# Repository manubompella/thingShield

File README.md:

# Arduino XBee shield

The Arduino shield is designed to be used for multiple use cases without redesigning the hardware. 

## Platform Features

 * [XBee Compatible Socket](https://www.sparkfun.com/datasheets/Wireless/Zigbee/XBee-Dimensional.pdf)
 * TTL to CMOS level shifter
 * Compatible with UNO R3 headers
 * Ability to support multiple thingBot platforms
 
## Maintainers

The Arduino Xbee shield is maintained by thingTronics Innovations.

Main contributor:
 * Manohar Bompella @<manohar.bompella@thingtronics.com>
 * Lovelesh Patel @<lovelesh.patel@thingtronics.com>

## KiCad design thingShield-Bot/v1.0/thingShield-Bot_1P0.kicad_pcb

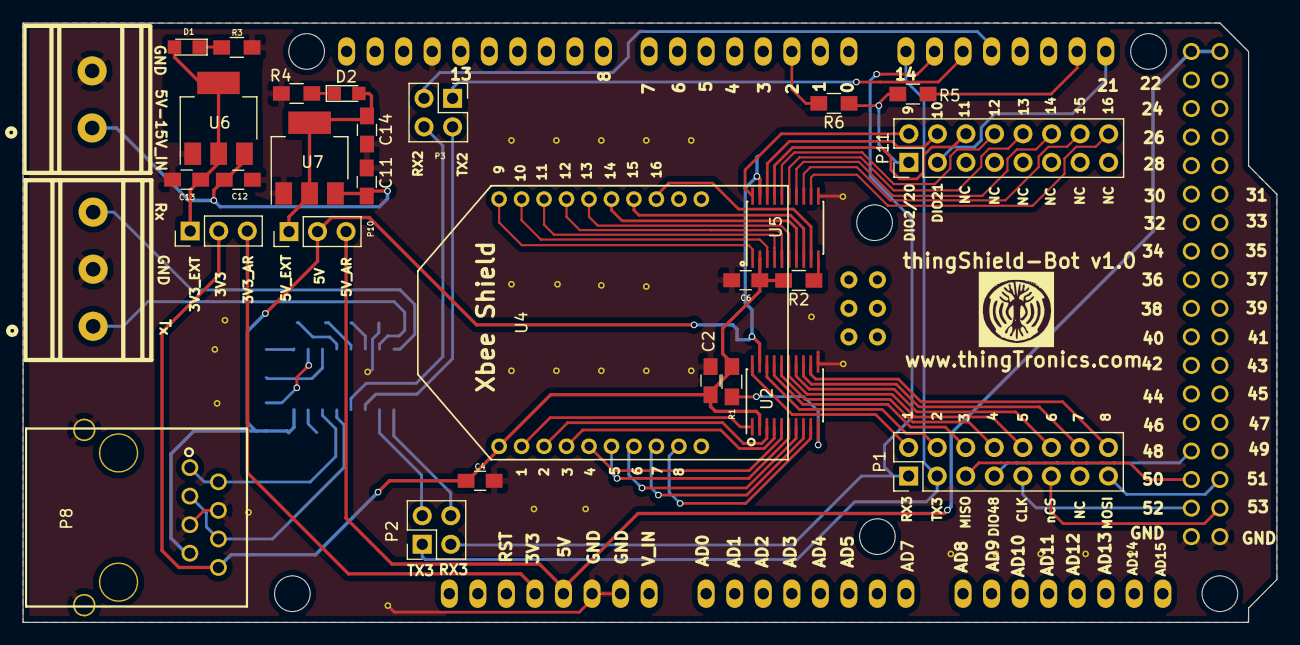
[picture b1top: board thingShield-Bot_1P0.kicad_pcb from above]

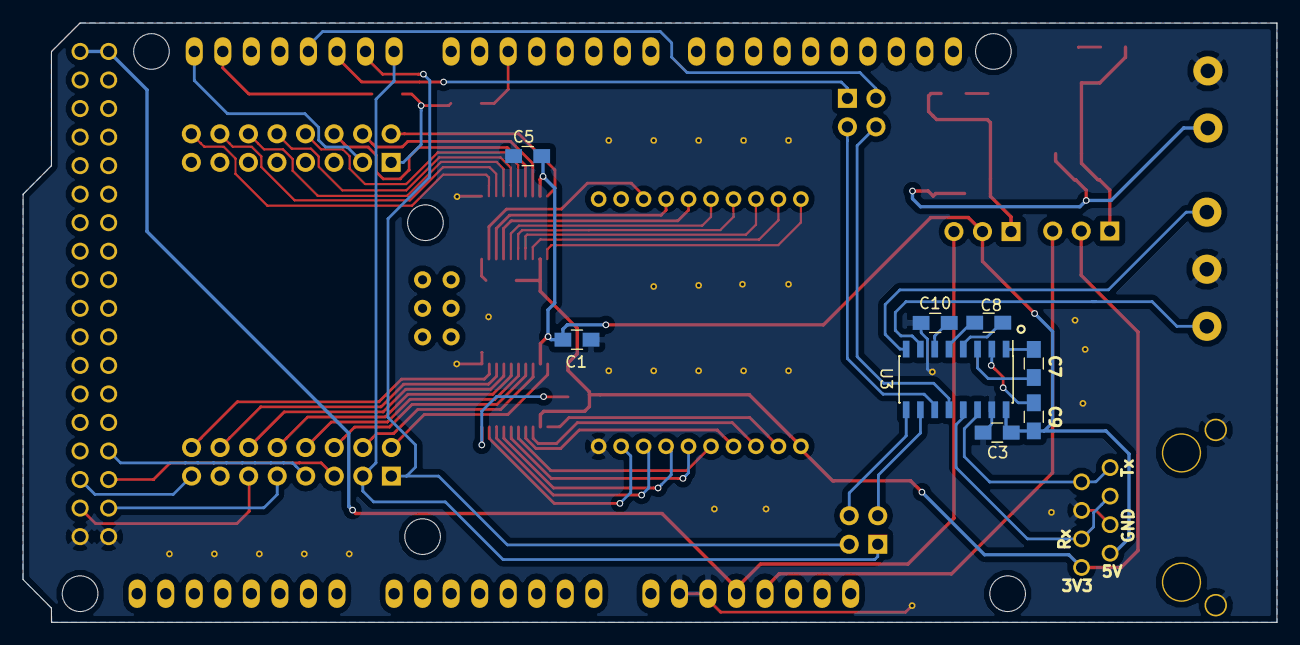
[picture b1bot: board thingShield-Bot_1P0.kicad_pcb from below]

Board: 2 copper layers, 111.6 x 53.3 mm, 38 parts (8 on the bottom side), 71 nets.

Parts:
C1, C2, C5, C6: 0.1uF; C_0805_HandSoldering
C3, C4, C7, C8, C9, C10: 1uF; C_0805_HandSoldering
C11, C12, C13, C14: 10uF; C_0805_HandSoldering
D1, D2: PWR; LED_0805
P1: LEFT_CONN_02X08; Pin_Header_Straight_2x08_Pitch2.54mm
P2: RS232_JMPR_2; Pin_Header_Straight_2x02_Pitch2.54mm
P3: RS232_JMPR_1; Pin_Header_Straight_2x02_Pitch2.54mm
P5: CONN_COM; gmkds_3-3-5,08
P6: JMPR_3V3; Pin_Header_Straight_1x03_Pitch2.54mm
P7: PWR_CONN; gmkds_3-2-5,08
P8: CNT-RJ45_10PIN; RJ45_18.7 X 15.84
P10: JMPR_5V; Pin_Header_Straight_1x03_Pitch2.54mm
P11: RIGHT_CONN_02X08; Pin_Header_Straight_2x08_Pitch2.54mm
R1, R2: 10K; R_0805_HandSoldering
R3, R4: 1K; R_0805_HandSoldering
R5, R6: 0E; R_0805_HandSoldering
U1: ARDUINO_MEGA_SHIELD
U2, U5: TXB0108; SSOP-20_4.4x6.5mm_Pitch0.65mm_longPads
U3: MAX232; SOIC-16_3.9x9.9mm_Pitch1.27mm
U4: XBEE_MODULE; XBee_Socket_without_Jtag
U6: LM1117-3.3; SOT-223
U7: LM1117-5.0; SOT-223

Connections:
3V3: C2.1, C4.1, C6.1, P6.2, P8.8, R1.2, R2.2, U2.2, U4.1, U5.2
3V3_AR: P6.3, U1.3V3
3V3_EXT: C13.1, D1.2, P6.1, U6.2, U6.4
5V: C1.1, C3.1, C5.1, C9.1, P8.7, P10.2, U2.19, U3.16, U5.19
5V_AR: P10.3, U1.5V, U1.5V_4, U1.5V_5
5V_EXT: C14.1, D2.2, P10.1, U7.2, U7.4
CLK: P1.9, U1.52
EXT_PWR_IN: C11.1, C12.1, P7.1, U6.3, U7.3
GND: C1.2, C2.2, C3.2, C4.2, C5.2, C6.2, C10.1, C11.2, C12.2, C13.2, C14.2, P5.2, P7.2, P8.4, P8.5, P8.9, P8.10, R3.2, R4.2, U1.GND1, U1.GND2, U1.GND3, U1.GND4, U1.GND5, U2.11, U3.15, U4.10, U5.11, U6.1, U7.1
INT_2: R6.2, U1.2
MISO: P1.5, U1.50
MOSI: P1.15, U1.51
unnamed: C7.1, U3.1
unnamed: C7.2, U3.3
unnamed: C8.1, U3.4
unnamed: C8.2, U3.5
unnamed: C9.2, U3.2
unnamed: C10.2, U3.6
unnamed: D1.1, R3.1
unnamed: D2.1, R4.1
unnamed: P1.2, U2.20
unnamed: P1.4, U2.18
unnamed: P1.6, U2.17
unnamed: P1.8, U2.16
unnamed: P1.10, U2.15
unnamed: P1.12, U2.14
unnamed: P1.14, U2.13
unnamed: P1.16, U2.12
unnamed: P2.2, U3.10
unnamed: P2.4, U3.9
unnamed: P3.2, U3.11
unnamed: P3.4, U3.12
unnamed: P11.1, R5.1, R6.1
unnamed: P11.2, U5.20
unnamed: P11.4, U5.18
unnamed: P11.6, U5.17
unnamed: P11.8, U5.16
unnamed: P11.10, U5.15
unnamed: P11.12, U5.14
unnamed: P11.14, U5.13
unnamed: P11.16, U5.12
unnamed: R1.1, U2.10
unnamed: R2.1, U5.10
unnamed: U2.1, U4.2
unnamed: U2.3, U4.3
unnamed: U2.4, U4.4
unnamed: U2.5, U4.5
unnamed: U2.6, U4.6
unnamed: U2.7, U4.7
unnamed: U2.8, U4.8
unnamed: U2.9, U4.9
unnamed: U4.13, U5.9
unnamed: U4.14, U5.8
unnamed: U4.15, U5.7
unnamed: U4.16, U5.6
unnamed: U4.17, U5.5
unnamed: U4.18, U5.4
unnamed: U4.19, U5.3
unnamed: U4.20, U5.1
RX2: P3.3, U1.17
RX3: P1.1, P2.3, U1.15
RX_232_1: P8.3, P8.6, U3.13
RX_232_2: P5.3, U3.8
SCL: P11.3, U1.21
SDA: R5.2, U1.20
TX2: P3.1, U1.16
TX3: P1.3, P2.1, U1.14
TX_232_1: P8.1, P8.2, U3.14
TX_232_2: P5.1, U3.7
nCS: P1.11, U1.53
nRESET: P1.7, U1.48

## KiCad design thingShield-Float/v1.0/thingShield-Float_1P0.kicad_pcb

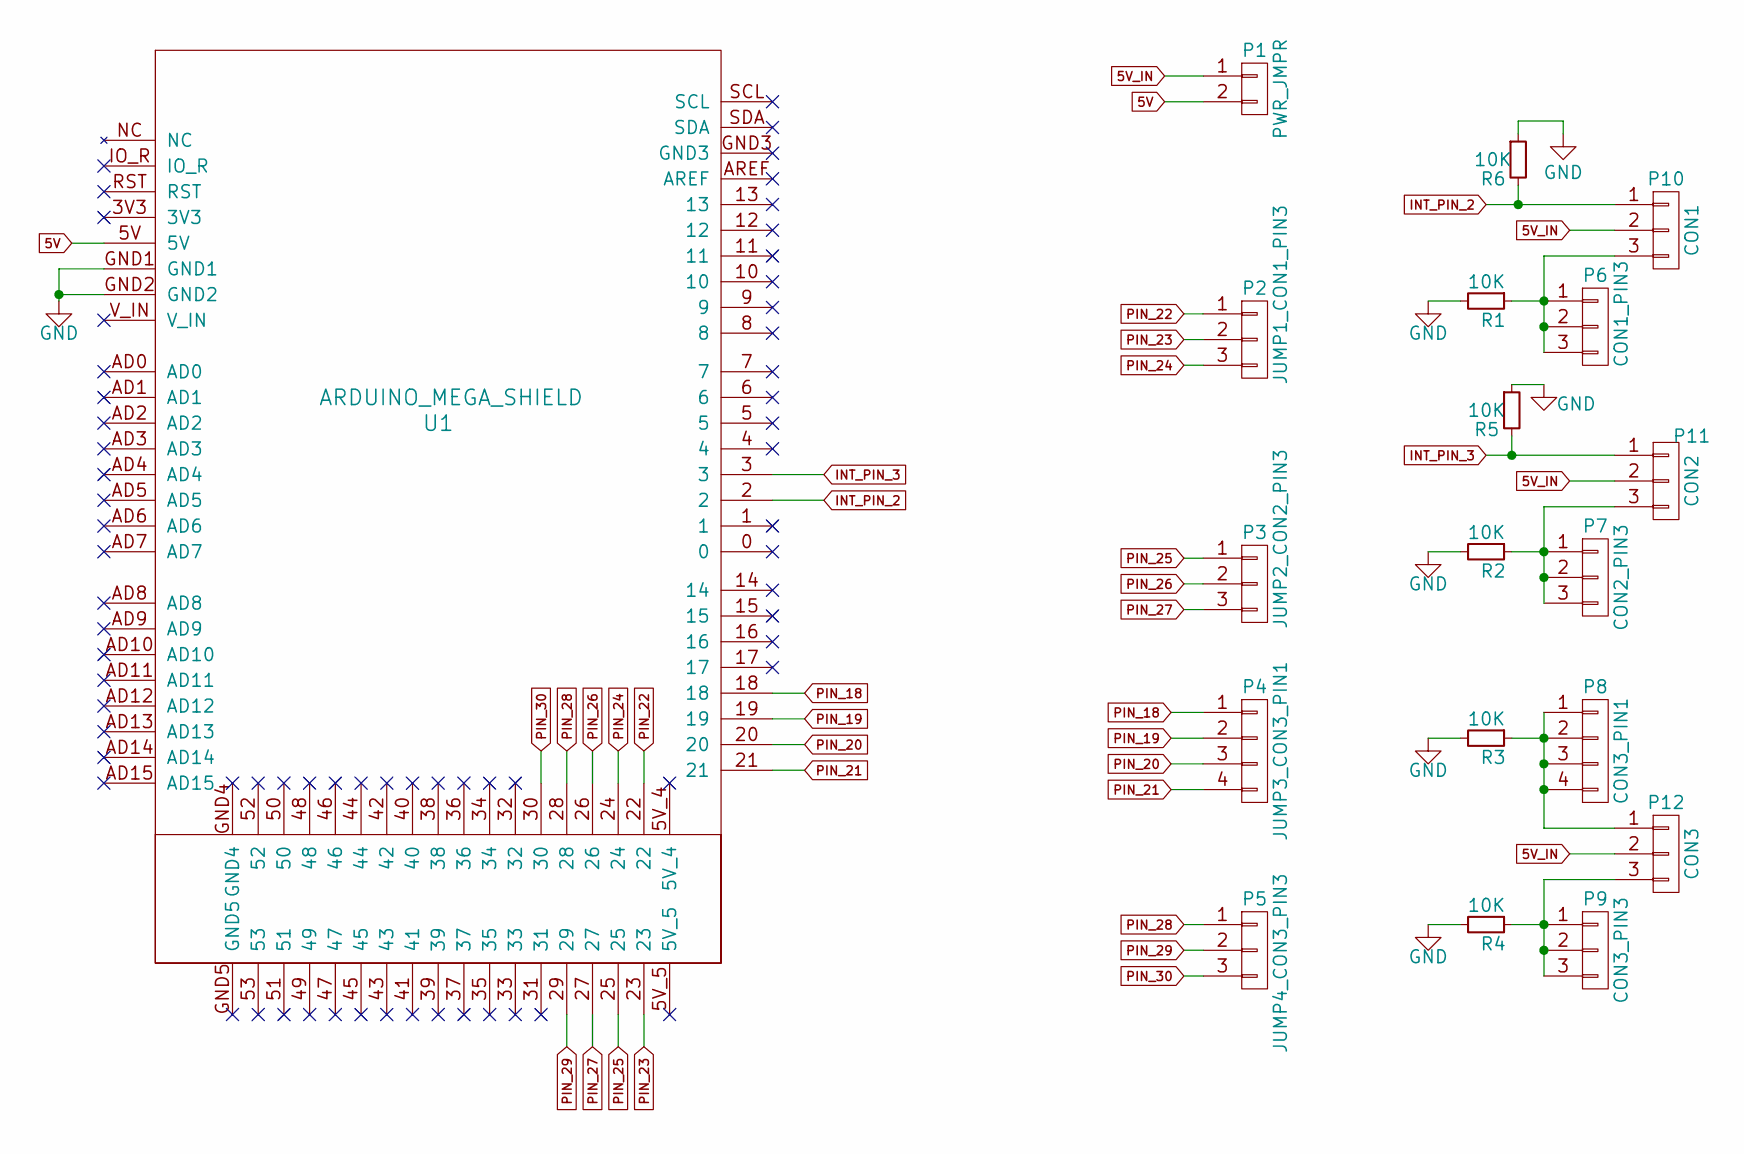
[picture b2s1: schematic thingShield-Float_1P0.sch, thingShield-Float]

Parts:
P1: PWR_JMPR; Pin_Header_Straight_1x02_Pitch2.54mm
P2: JUMP1_CON1_PIN3; Pin_Header_Straight_1x03_Pitch2.54mm
P3: JUMP2_CON2_PIN3; Pin_Header_Straight_1x03_Pitch2.54mm
P4: JUMP3_CON3_PIN1; Pin_Header_Straight_1x04_Pitch2.54mm
P5: JUMP4_CON3_PIN3; Pin_Header_Straight_1x03_Pitch2.54mm
P6: CON1_PIN3; Pin_Header_Straight_1x03_Pitch2.54mm
P7: CON2_PIN3; Pin_Header_Straight_1x03_Pitch2.54mm
P8: CON3_PIN1; Pin_Header_Straight_1x04_Pitch2.54mm
P9: CON3_PIN3; Pin_Header_Straight_1x03_Pitch2.54mm
P10: CON1; gmkds_3-3-5,08
P11: CON2; gmkds_3-3-5,08
P12: CON3; gmkds_3-3-5,08
R1, R2, R3, R4, R5, R6: 10K; R_0805_HandSoldering
U1: ARDUINO_MEGA_SHIELD

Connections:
5V: P1.2, U1.5V
5V_IN: P1.1, P10.2, P11.2, P12.2
GND: R1.2, R2.2, R3.2, R4.2, R5.1, R6.1, U1.GND1, U1.GND2
INT_PIN_2: P10.1, R6.2, U1.2
INT_PIN_3: P11.1, R5.2, U1.3
unnamed: P6.1, P6.2, P6.3, P10.3, R1.1
unnamed: P7.1, P7.2, P7.3, P11.3, R2.1
unnamed: P8.1, P8.2, P8.3, P8.4, P12.1, R3.1
unnamed: P9.1, P9.2, P9.3, P12.3, R4.1
PIN_18: P4.1, U1.18
PIN_19: P4.2, U1.19
PIN_20: P4.3, U1.20
PIN_21: P4.4, U1.21
PIN_22: P2.1, U1.22
PIN_23: P2.2, U1.23
PIN_24: P2.3, U1.24
PIN_25: P3.1, U1.25
PIN_26: P3.2, U1.26
PIN_27: P3.3, U1.27
PIN_28: P5.1, U1.28
PIN_29: P5.2, U1.29
PIN_30: P5.3, U1.30

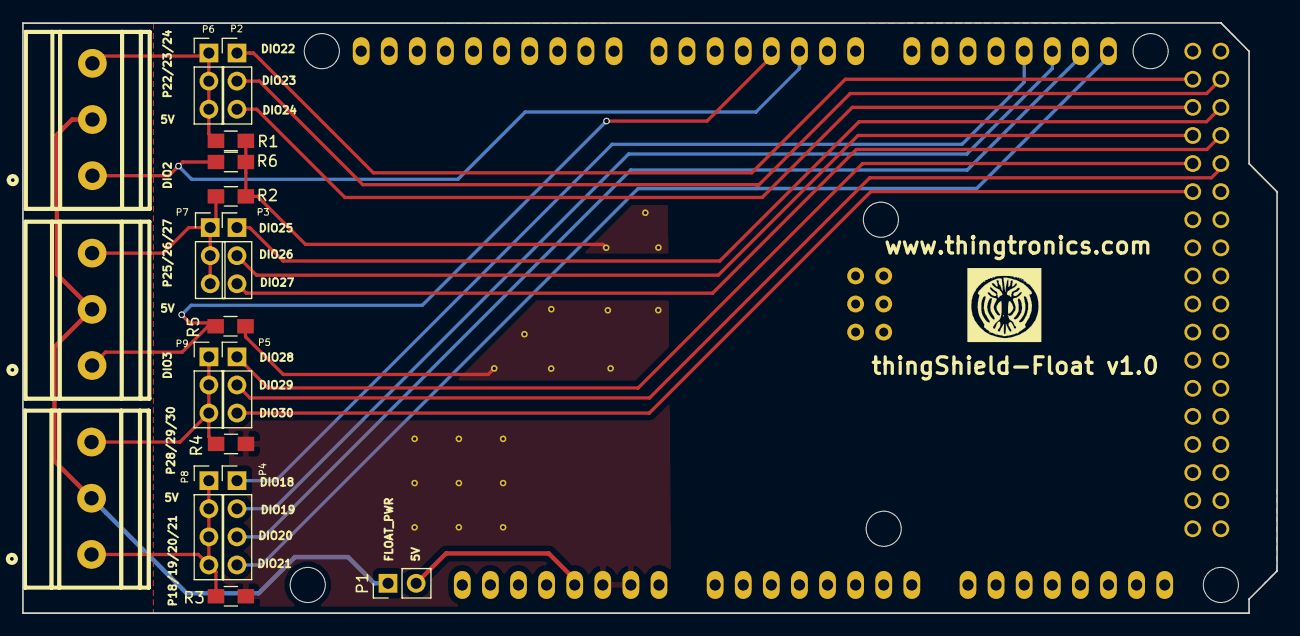
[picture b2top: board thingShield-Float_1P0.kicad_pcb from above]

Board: 2 copper layers, 113.4 x 53.4 mm, 19 parts (0 on the bottom side), 22 nets.

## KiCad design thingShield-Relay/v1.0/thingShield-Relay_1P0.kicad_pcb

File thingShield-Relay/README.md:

# thingRelay-Shield

The Arduino shield is designed to be used for relay without redesigning the hardware. 

## Platform Features

 * Compatible with UNO R3/MEGA headers
 
## Maintainers

The thingRelay-Shield is maintained by thingTronics Innovations.

Main contributor:
 * Manohar Bompella @<manohar.bompella@thingtronics.com>
 * Lovelesh Patel @<lovelesh.patel@thingtronics.com>

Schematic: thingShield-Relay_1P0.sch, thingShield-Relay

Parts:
D1, D2: YELLOW; LED_0805
D3, D4: znr diode; D_5W_P10.16mm_Horizontal
P1: MEGA_PIN_MAPING; Pin_Header_Straight_1x12_Pitch2.54mm
P2: RELAY_2_PIN_HEADER; Pin_Header_Straight_1x12_Pitch2.54mm
P3: 5V_TO_RELAY_VCC_CONN; Pin_Header_Straight_1x02_Pitch2.54mm
P4: RELAY_1_PIN_HEADER; Pin_Header_Straight_1x12_Pitch2.54mm
P5: RELAY_2_CON; gmkds_3-3-5,08
P6: RELAY_1_CON; gmkds_3-3-5,08
P7: EXT_PWR; gmkds_3-2-5,08
Q1, Q2: MMBT3904; SOT-23
R1, R2: 1K; R_0805_HandSoldering
R3, R4: 510E; R_0805_HandSoldering
RL1: RELAY_1; Songle_SRS-03VDC-SL
RL2: RELAY_2; Songle_SRS-03VDC-SL
U1: ARDUINO_MEGA_SHIELD
U2, U3: LTV-817; DIL04

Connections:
5V: P3.2, U1.5V
GND: P7.2, Q1.2 (E), Q2.2 (E), U1.GND1
unnamed: D1.2 (A), U2.2
unnamed: D2.2 (A), U3.2
unnamed: D3.2 (A), Q1.3 (C), RL1.1
unnamed: D4.2 (A), Q2.3 (C), RL2.1
unnamed: P1.1, U1.13
unnamed: P1.2, U1.12
unnamed: P1.3, U1.11
unnamed: P1.4, U1.10
unnamed: P1.5, U1.9
unnamed: P1.6, U1.8
unnamed: P1.7, U1.7
unnamed: P1.8, U1.6
unnamed: P1.9, U1.5
unnamed: P1.10, U1.4
unnamed: P1.11, U1.3
unnamed: P1.12, U1.2
unnamed: P5.1, RL2.4
unnamed: P5.2, RL2.3
unnamed: P5.3, RL2.5
unnamed: P6.1, RL1.4
unnamed: P6.2, RL1.3
unnamed: P6.3, RL1.5
unnamed: Q1.1 (B), R3.1
unnamed: Q2.1 (B), R4.1
unnamed: R1.1, U2.1
unnamed: R2.1, U3.1
unnamed: R3.2, U2.3
unnamed: R4.2, U3.3
RELAY_1: D1.1 (K), P4.1, P4.2, P4.3, P4.4, P4.5, P4.6, P4.7, P4.8, P4.9, P4.10, P4.11, P4.12
RELAY_2: D2.1 (K), P2.1, P2.2, P2.3, P2.4, P2.5, P2.6, P2.7, P2.8, P2.9, P2.10, P2.11, P2.12
RELAY_VCC: D3.1 (K), D4.1 (K), P3.1, P7.1, R1.2, R2.2, RL1.2, RL2.2, U2.4, U3.4

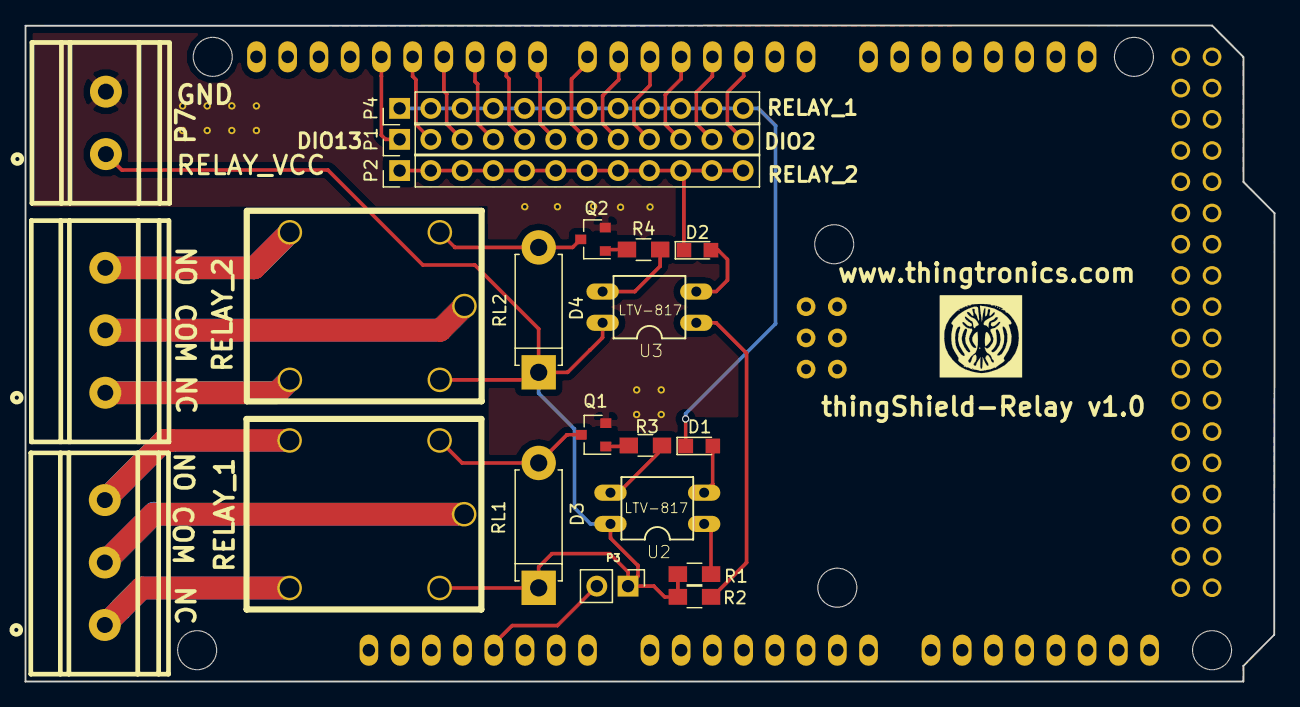
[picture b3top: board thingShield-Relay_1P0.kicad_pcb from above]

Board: 2 copper layers, 101.6 x 53.4 mm, 22 parts (0 on the bottom side), 33 nets.

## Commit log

2017-03-09 :octocat: Added .gitattributes & .gitignore files
2017-03-09 initiated the schematic design
2017-05-04 three thingShield projects added
    the following thingShield added
    -> thingBot-Shield
    -> thingFloat-Shield
    -> thingRelay-Shield
    in each of them Bom,gerbers,reference,schematic and layout files added
2017-05-04 three thingBot-shield projects added
    following shields added
    -> thingBot-Shield
    -> thingFloat-Shield
    -> thingRelay-Shield
    in each one bom ,reference,gerbers files added
2017-05-27 Verified Bot and float shields
2017-05-27 verified all the shields
2017-05-31 thingBot-Shieldv2.0 files added
    thingBot-Shieldv2.0 following files added
    - schematic
    - Layout
    - gerber files added
2017-05-31 removed v2.0
    removed v2.0
2017-05-31 removed unrequired images
    removed unrequired images
2017-05-31 thingShield-Bot v2.0 files added
    thingShield-Bot v2.0 following things Added
    - shcematic
    - layout
    - gerbers
